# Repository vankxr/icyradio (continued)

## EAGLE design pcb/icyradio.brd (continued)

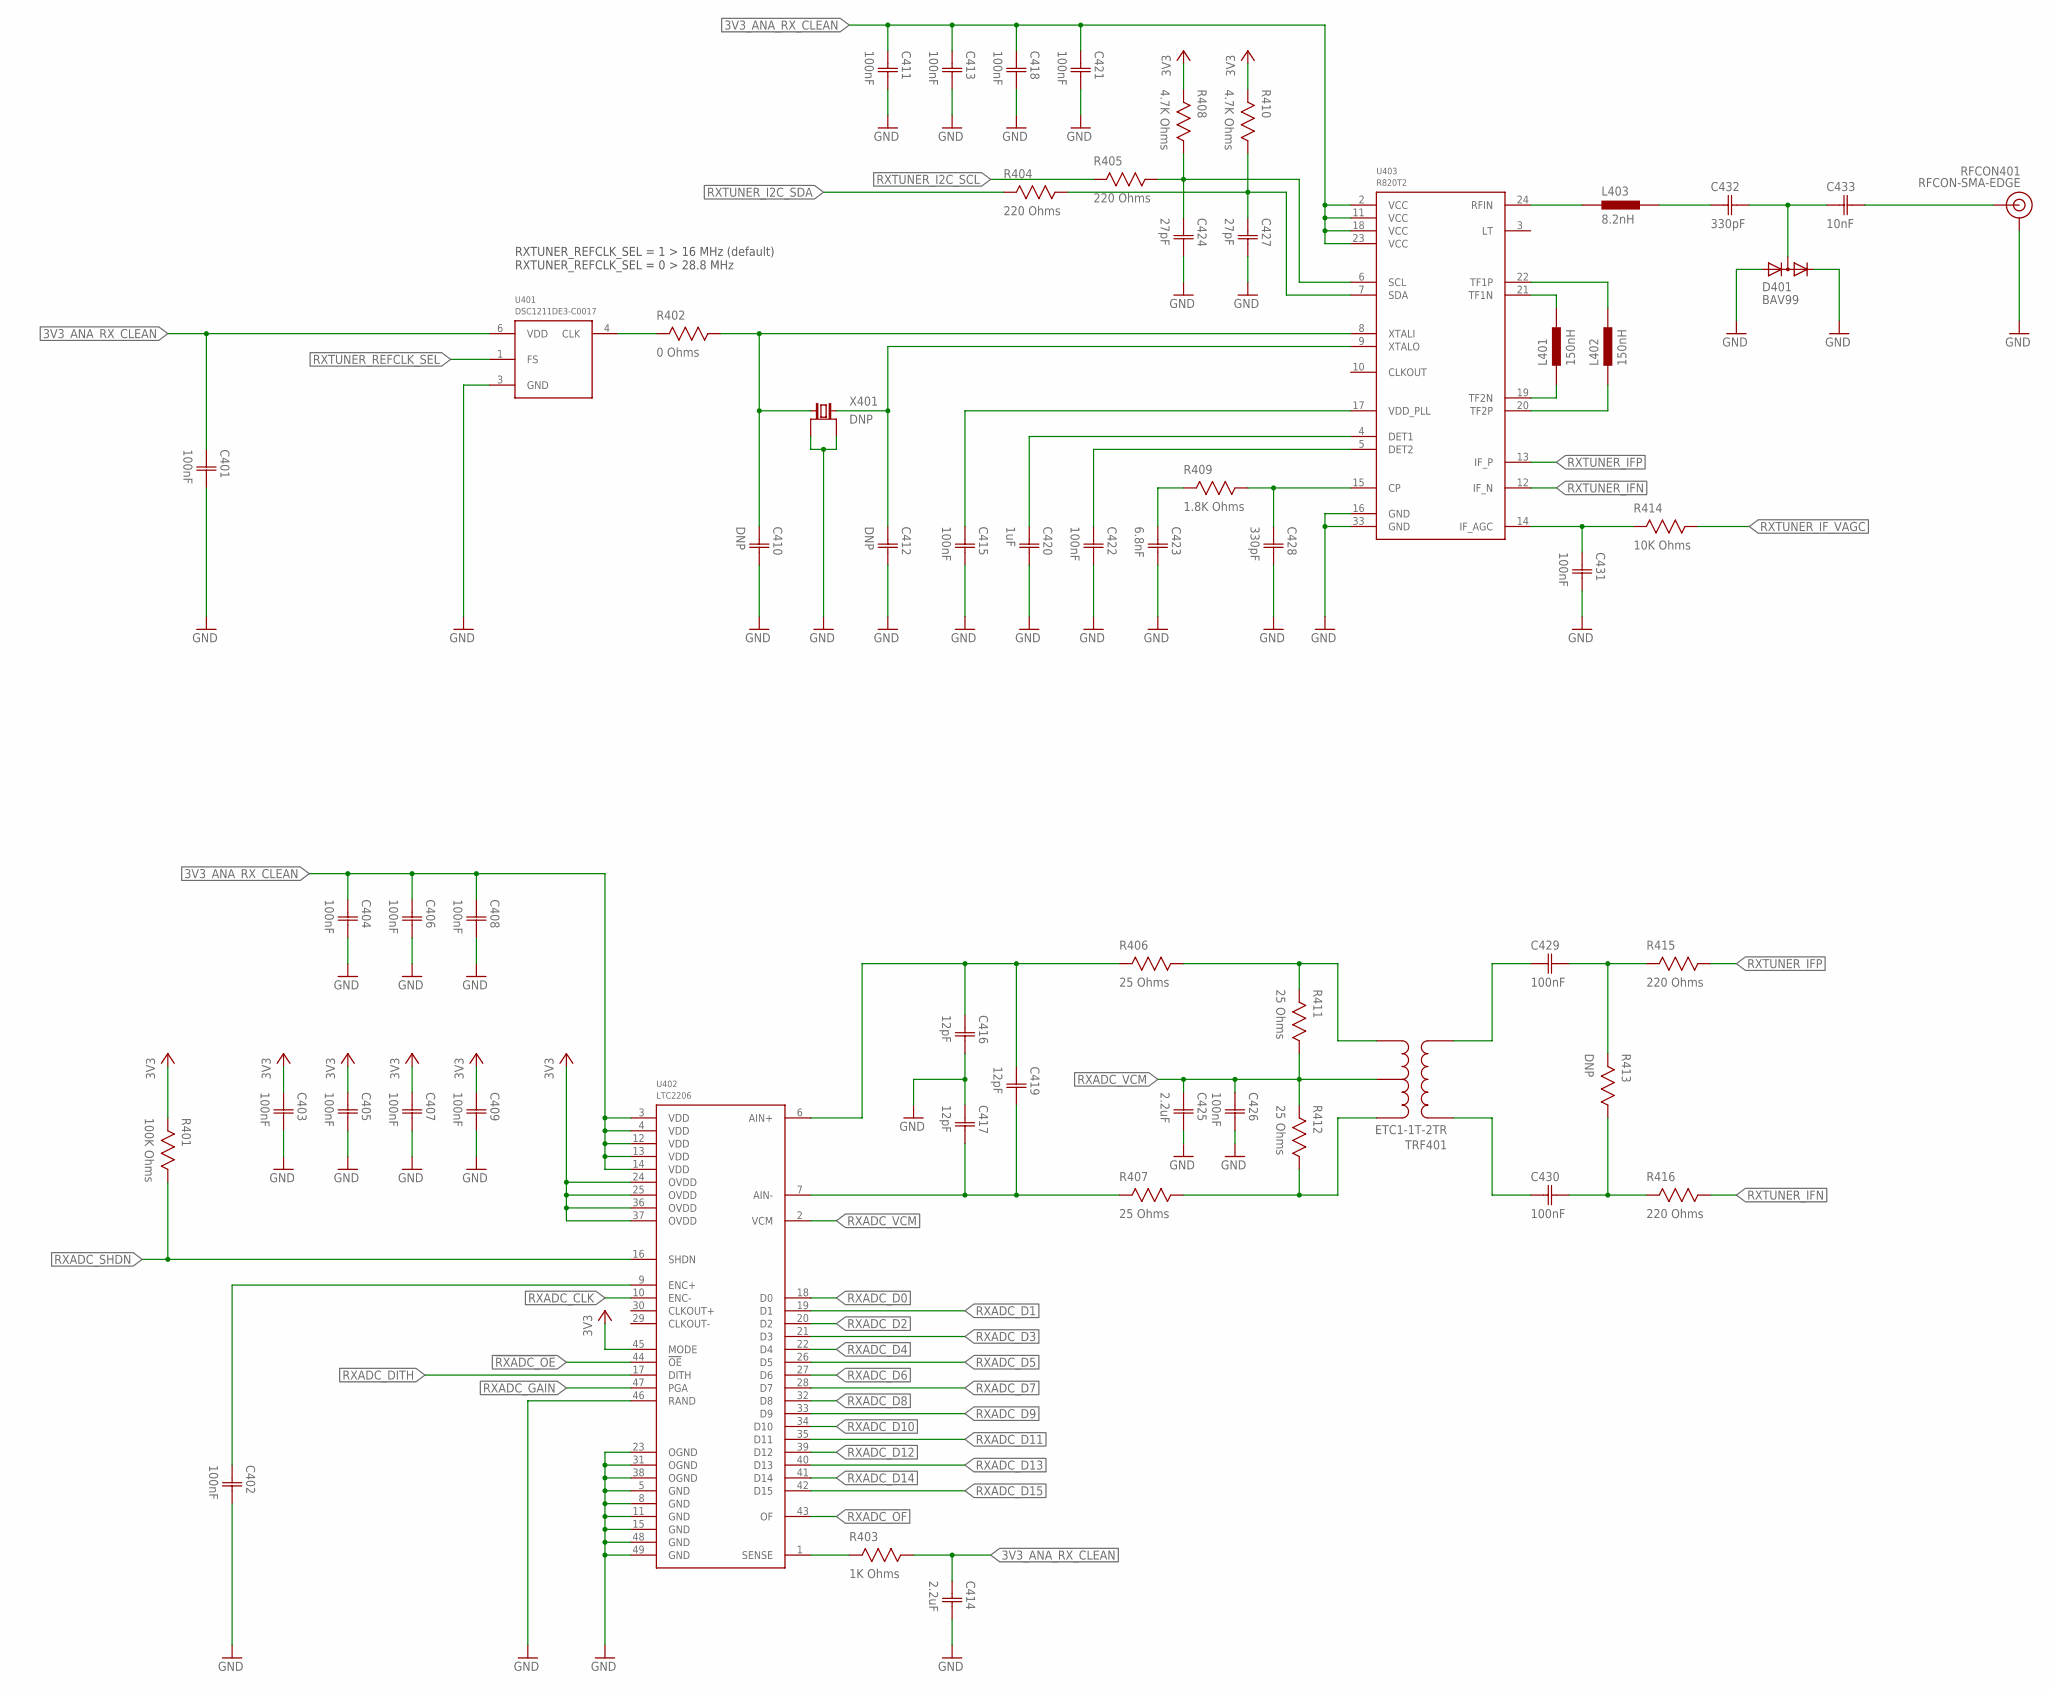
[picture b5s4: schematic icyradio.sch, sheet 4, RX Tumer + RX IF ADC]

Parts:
C401, C402, C403, C404, C405, C406, C407, C408, C409, C411, C413, C415, C418, C421, C422, C426, C429, C430, C431: 100nF; CAP0603
C410, C412: DNP; CAP0603
C414, C425: 2.2uF; CAP0603
C416, C417, C419: 12pF; CAP0603
C420: 1uF; CAP0603
C423: 6.8nF; CAP0603
C424, C427: 27pF; CAP0603
C428, C432: 330pF; CAP0603
C433: 10nF; CAP0603
D401: BAV99; SOT23
L401, L402: 150nH; IND0603
L403: 8.2nH; IND0603
R401: 100K Ohms; RES0603
R402: 0 Ohms; RES0603
R403: 1K Ohms; RES0603
R404, R405, R415, R416: 220 Ohms; RES0603
R406, R407, R411, R412: 25 Ohms; RES0603
R408, R410: 4.7K Ohms; RES0603
R409: 1.8K Ohms; RES0603
R413: DNP; RES0603
R414: 10K Ohms; RES0603
RFCON401: RFCON-SMA-EDGE; SMA-EDGE
TRF401: ETC1-1T-2TR; TRF-SM-22
U401: DSC1211DE3-C0017; VDFN6
U402: LTC2206; QFN48
U403: R820T2; QFN24
X401: DNP; 4-SMD-3225

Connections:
3V3: C403.1 (C1), C405.1 (C1), C407.1 (C1), C409.1 (C1), R401.2, R408.2, R410.2, U402.24 (OVDD), U402.25 (OVDD), U402.36 (OVDD), U402.37 (OVDD), U402.45 (MODE); also elsewhere on the board
3V3_ANA_RX_CLEAN: C401.1 (C1), C404.1 (C1), C406.1 (C1), C408.1 (C1), C411.1 (C1), C413.1 (C1), C414.1 (C1), C418.1 (C1), C421.1 (C1), R403.1, U401.6 (VDD), U402.3 (VDD), U402.4 (VDD), U402.12 (VDD), U402.13 (VDD), U402.14 (VDD), U403.2 (VCC), U403.11 (VCC), U403.18 (VCC), U403.23 (VCC); also elsewhere on the board
!RXADC_OE: U402.44 (!OE); also elsewhere on the board
GND: C401.2 (C2), C402.2 (C2), C403.2 (C2), C404.2 (C2), C405.2 (C2), C406.2 (C2), C407.2 (C2), C408.2 (C2), C409.2 (C2), C410.2 (C2), C411.2 (C2), C412.2 (C2), C413.2 (C2), C414.2 (C2), C415.2 (C2), C416.2 (C2), C417.1 (C1), C418.2 (C2), C420.2 (C2), C421.2 (C2), C422.2 (C2), C423.2 (C2), C424.2 (C2), C425.2 (C2), C426.2 (C2), C427.2 (C2), C428.2 (C2), C431.2 (C2), D401.1 (A), D401.2 (C), RFCON401.GND@0 (GND), RFCON401.GND@1 (GND), RFCON401.GND@2 (GND), RFCON401.GND@3 (GND), U401.3 (GND), U402.5 (GND), U402.8 (GND), U402.11 (GND), U402.15 (GND), U402.23 (OGND), U402.31 (OGND), U402.38 (OGND), U402.46 (RAND), U402.48 (GND), U402.49 (GND), U403.16 (GND), U403.33 (GND), X401.1 (GND), X401.3 (GND); also elsewhere on the board
unnamed: R407.1, R412.1, TRF401.3 (SEC1)
unnamed: C430.1 (C1), TRF401.4 (PRI1)
unnamed: R406.1, R411.2, TRF401.1 (SEC2)
unnamed: C429.1 (C1), TRF401.5 (PRI2)
unnamed: C430.2 (C2), R413.1, R416.2
unnamed: C429.2 (C2), R413.2, R415.2
unnamed: C433.2 (C2), RFCON401.SIG (SIGNAL)
unnamed: C432.2 (C2), C433.1 (C1), D401.3 (MID)
unnamed: C432.1 (C1), L403.2
unnamed: L403.1, U403.24 (RFIN)
unnamed: C424.1 (C1), R405.1, R408.1, U403.6 (SCL)
unnamed: C427.1 (C1), R404.1, R410.1, U403.7 (SDA)
unnamed: C423.1 (C1), R409.2
unnamed: R402.2, U401.4 (CLK)
unnamed: C431.1 (C1), R414.2, U403.14 (IF_AGC)
RXADC_AIN+: C416.1 (C1), C419.1 (C1), R406.2, U402.6 (AIN+)
RXADC_AIN-: C417.2 (C2), C419.2 (C2), R407.2, U402.7 (AIN-)
RXADC_CLK: U402.10 (ENC-); also elsewhere on the board
RXADC_D0: U402.18 (D0); also elsewhere on the board
RXADC_D1: U402.19 (D1); also elsewhere on the board
RXADC_D2: U402.20 (D2); also elsewhere on the board
RXADC_D3: U402.21 (D3); also elsewhere on the board
RXADC_D4: U402.22 (D4); also elsewhere on the board
RXADC_D5: U402.26 (D5); also elsewhere on the board
RXADC_D6: U402.27 (D6); also elsewhere on the board
RXADC_D7: U402.28 (D7); also elsewhere on the board
RXADC_D8: U402.32 (D8); also elsewhere on the board
RXADC_D9: U402.33 (D9); also elsewhere on the board
RXADC_D10: U402.34 (D10); also elsewhere on the board
RXADC_D11: U402.35 (D11); also elsewhere on the board
RXADC_D12: U402.39 (D12); also elsewhere on the board
RXADC_D13: U402.40 (D13); also elsewhere on the board
RXADC_D14: U402.41 (D14); also elsewhere on the board
RXADC_D15: U402.42 (D15); also elsewhere on the board
RXADC_DITH: U402.17 (DITH); also elsewhere on the board
RXADC_ENC+: C402.1 (C1), U402.9 (ENC+)
RXADC_GAIN: U402.47 (PGA); also elsewhere on the board
RXADC_OF: U402.43 (OF); also elsewhere on the board
RXADC_SENSE: R403.2, U402.1 (SENSE)
RXADC_SHDN: R401.1, U402.16 (SHDN); also elsewhere on the board
RXADC_VCM: C425.1 (C1), C426.1 (C1), R411.1, R412.2, TRF401.2 (CT), U402.2 (VCM)
RXTUNER_DET1: C420.1 (C1), U403.4 (DET1)
RXTUNER_DET2: C422.1 (C1), U403.5 (DET2)
RXTUNER_I2C_SCL: R405.2; also elsewhere on the board
RXTUNER_I2C_SDA: R404.2; also elsewhere on the board
RXTUNER_IFN: R416.1, U403.12 (IF_N)
RXTUNER_IFP: R415.1, U403.13 (IF_P)
RXTUNER_IF_VAGC: R414.1; also elsewhere on the board
RXTUNER_PLL_CP: C428.1 (C1), R409.1, U403.15 (CP)
RXTUNER_REFCLK_SEL: U401.1 (FS); also elsewhere on the board
RXTUNER_TF1N: L401.2, U403.21 (TF1N)
RXTUNER_TF1P: L402.2, U403.22 (TF1P)
RXTUNER_TF2N: L401.1, U403.19 (TF2N)
RXTUNER_TF2P: L402.1, U403.20 (TF2P)
RXTUNER_VDD_PLL: C415.1 (C1), U403.17 (VDD_PLL)
RXTUNER_XTALI: C410.1 (C1), R402.1, U403.8 (XTALI), X401.2 (1)
RXTUNER_XTALO: C412.1 (C1), U403.9 (XTALO), X401.4 (2)

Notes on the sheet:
RXTUNER_REFCLK_SEL = 1 > 16 MHz (default) RXTUNER_REFCLK_SEL = 0 > 28.8 MHz

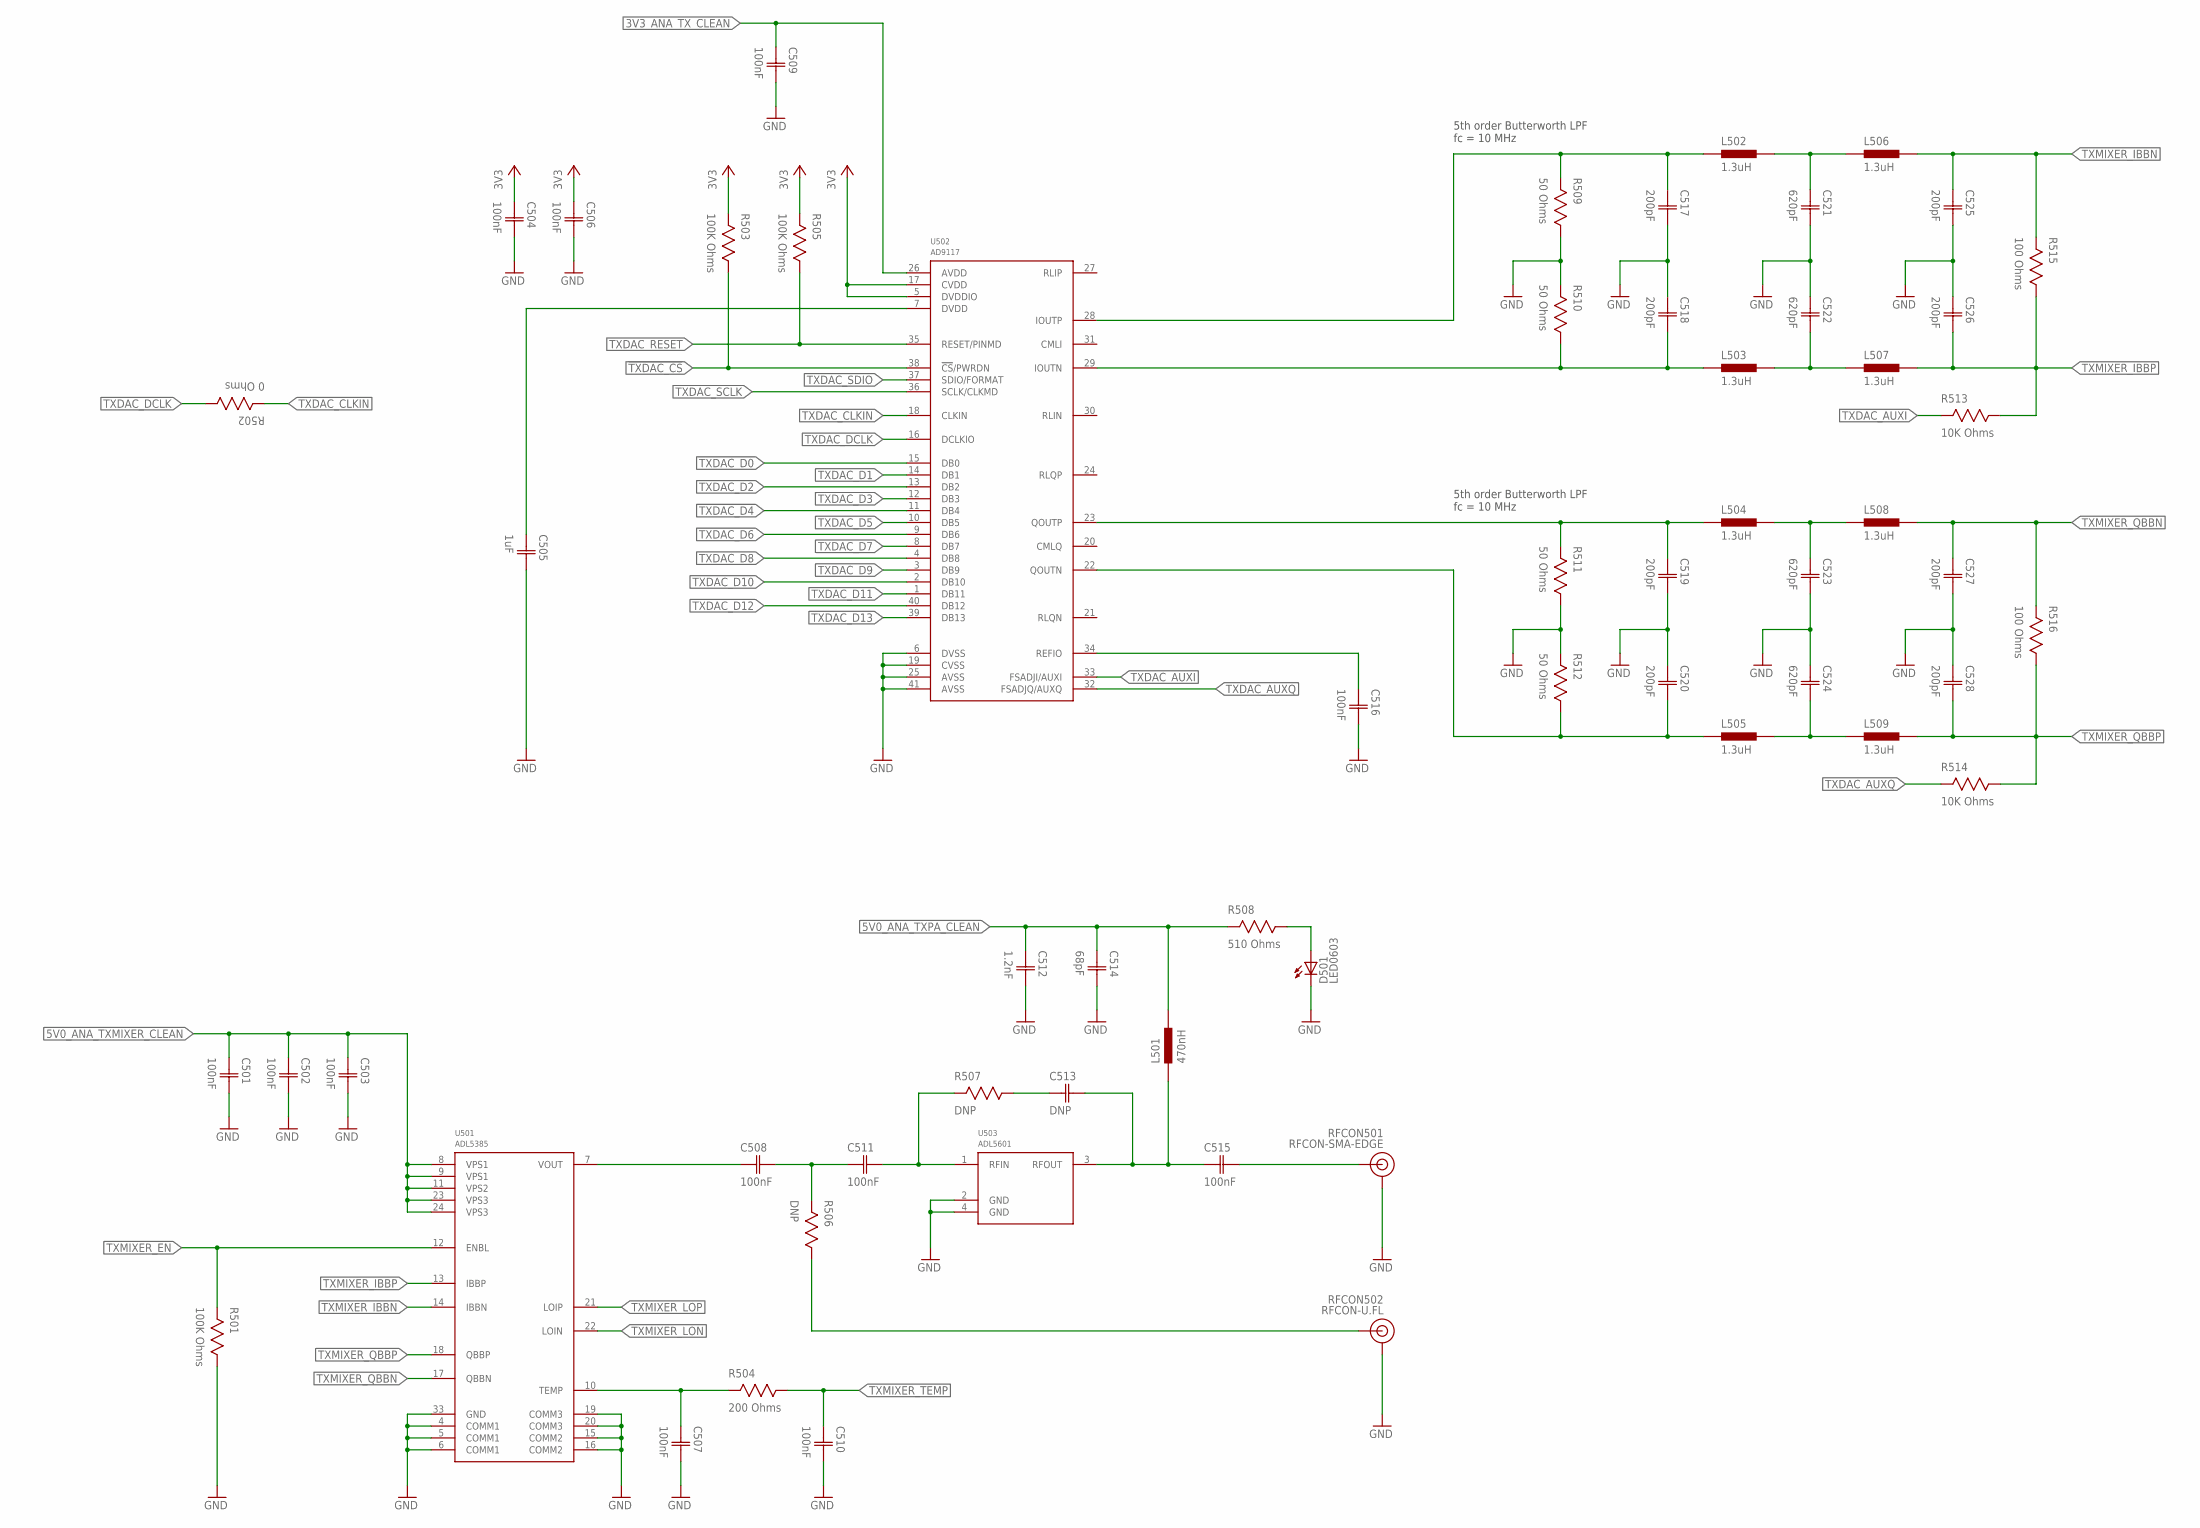
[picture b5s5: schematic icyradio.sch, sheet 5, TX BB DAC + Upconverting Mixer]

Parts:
C501, C502, C503, C504, C506, C507, C508, C509, C510, C511, C515, C516: 100nF; CAP0603
C505: 1uF; CAP0603
C512: 1.2nF; CAP0603
C513: DNP; CAP0603
C514: 68pF; CAP0603
C517, C518, C519, C520, C525, C526, C527, C528: 200pF; CAP0603
C521, C522, C523, C524: 620pF; CAP0603
D501: LED0603; 0603
L501: 470nH; IND0603
L502, L503, L504, L505, L506, L507, L508, L509: 1.3uH; IND0603
R501, R503, R505: 100K Ohms; RES0603
R502: 0 Ohms; RES0603
R504: 200 Ohms; RES0603
R506, R507: DNP; RES0603
R508: 510 Ohms; RES0603
R509, R510, R511, R512: 50 Ohms; RES0603
R513, R514: 10K Ohms; RES0603
R515, R516: 100 Ohms; RES0603
RFCON501: RFCON-SMA-EDGE; SMA-EDGE
RFCON502: RFCON-U.FL; U.FL
U501: ADL5385; QFN24
U502: AD9117; QFN40
U503: ADL5601; SOT89

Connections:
3V3: C504.1 (C1), C506.1 (C1), R503.2, R505.2, U502.5 (DVDDIO), U502.17 (CVDD); also elsewhere on the board
3V3_ANA_TX_CLEAN: C509.1 (C1), U502.26 (AVDD); also elsewhere on the board
5V0_ANA_TXMIXER_CLEAN: C501.1 (C1), C502.1 (C1), C503.1 (C1), U501.8 (VPS1), U501.9 (VPS1), U501.11 (VPS2), U501.23 (VPS3), U501.24 (VPS3); also elsewhere on the board
5V0_ANA_TXPA_CLEAN: C512.1 (C1), C514.1 (C1), L501.2, R508.2; also elsewhere on the board
!TXDAC_CS: R503.1, U502.38 (!CS!/PWRDN); also elsewhere on the board
GND: C501.2 (C2), C502.2 (C2), C503.2 (C2), C504.2 (C2), C505.2 (C2), C506.2 (C2), C507.2 (C2), C509.2 (C2), C510.2 (C2), C512.2 (C2), C514.2 (C2), C516.2 (C2), C517.2 (C2), C518.1 (C1), C519.2 (C2), C520.1 (C1), C521.2 (C2), C522.1 (C1), C523.2 (C2), C524.1 (C1), C525.2 (C2), C526.1 (C1), C527.2 (C2), C528.1 (C1), D501.1 (C), R501.1, R509.1, R510.2, R511.1, R512.2, RFCON501.GND@0 (GND), RFCON501.GND@1 (GND), RFCON501.GND@2 (GND), RFCON501.GND@3 (GND), RFCON502.P$1 (GND), RFCON502.P$2 (GND), U501.4 (COMM1), U501.5 (COMM1), U501.6 (COMM1), U501.15 (COMM2), U501.16 (COMM2), U501.19 (COMM3), U501.20 (COMM3), U501.33 (GND), U502.6 (DVSS), U502.19 (CVSS), U502.20 (CMLQ), U502.25 (AVSS), U502.31 (CMLI), U502.41 (AVSS), U503.2 (GND), U503.4 (GND); also elsewhere on the board
unnamed: C508.2 (C2), C511.1 (C1), R506.2
unnamed: C507.1 (C1), R504.2, U501.10 (TEMP)
unnamed: C515.2 (C2), RFCON501.SIG (SIGNAL)
unnamed: C508.1 (C1), U501.7 (VOUT)
unnamed: C518.2 (C2), L503.1, R510.1, U502.29 (IOUTN)
unnamed: C517.1 (C1), L502.1, R509.2, U502.28 (IOUTP)
unnamed: C522.2 (C2), L503.2, L507.1
unnamed: C521.1 (C1), L502.2, L506.1
unnamed: C505.1 (C1), U502.7 (DVDD)
unnamed: C520.2 (C2), L505.1, R512.1, U502.22 (QOUTN)
unnamed: C519.1 (C1), L504.1, R511.2, U502.23 (QOUTP)
unnamed: C524.2 (C2), L505.2, L509.1
unnamed: C523.1 (C1), L504.2, L508.1
unnamed: C513.1 (C1), R507.1
unnamed: C516.1 (C1), U502.34 (REFIO)
unnamed: D501.2 (A), R508.1
TXDAC_AUXI: R513.2, U502.33 (FSADJI/AUXI)
TXDAC_AUXQ: R514.2, U502.32 (FSADJQ/AUXQ)
TXDAC_CLKIN: R502.2, U502.18 (CLKIN); also elsewhere on the board
TXDAC_D0: U502.15 (DB0); also elsewhere on the board
TXDAC_D1: U502.14 (DB1); also elsewhere on the board
TXDAC_D2: U502.13 (DB2); also elsewhere on the board
TXDAC_D3: U502.12 (DB3); also elsewhere on the board
TXDAC_D4: U502.11 (DB4); also elsewhere on the board
TXDAC_D5: U502.10 (DB5); also elsewhere on the board
TXDAC_D6: U502.9 (DB6); also elsewhere on the board
TXDAC_D7: U502.8 (DB7); also elsewhere on the board
TXDAC_D8: U502.4 (DB8); also elsewhere on the board
TXDAC_D9: U502.3 (DB9); also elsewhere on the board
TXDAC_D10: U502.2 (DB10); also elsewhere on the board
TXDAC_D11: U502.1 (DB11); also elsewhere on the board
TXDAC_D12: U502.40 (DB12); also elsewhere on the board
TXDAC_D13: U502.39 (DB13); also elsewhere on the board
TXDAC_DCLK: R502.1, U502.16 (DCLKIO); also elsewhere on the board
TXDAC_RESET: R505.1, U502.35 (RESET/PINMD); also elsewhere on the board
TXDAC_SCLK: U502.36 (SCLK/CLKMD); also elsewhere on the board
TXDAC_SDIO: U502.37 (SDIO/FORMAT); also elsewhere on the board
TXMIXER_EN: R501.2, U501.12 (ENBL); also elsewhere on the board
TXMIXER_IBBN: C525.1 (C1), L506.2, R515.2, U501.14 (IBBN)
TXMIXER_IBBP: C526.2 (C2), L507.2, R513.1, R515.1, U501.13 (IBBP)
TXMIXER_LON: U501.22 (LOIN); also elsewhere on the board
TXMIXER_LOP: U501.21 (LOIP); also elsewhere on the board
TXMIXER_OUT: R506.1, RFCON502.P$3 (SIGNAL)
TXMIXER_QBBN: C527.1 (C1), L508.2, R516.2, U501.17 (QBBN)
TXMIXER_QBBP: C528.2 (C2), L509.2, R514.1, R516.1, U501.18 (QBBP)
TXMIXER_TEMP: C510.1 (C1), R504.1; also elsewhere on the board
TXPA_IN: C511.2 (C2), R507.2, U503.1 (RFIN)
TXPA_OUT: C513.2 (C2), C515.1 (C1), L501.1, U503.3 (RFOUT)

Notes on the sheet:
5th order Butterworth LPF fc = 10 MHz

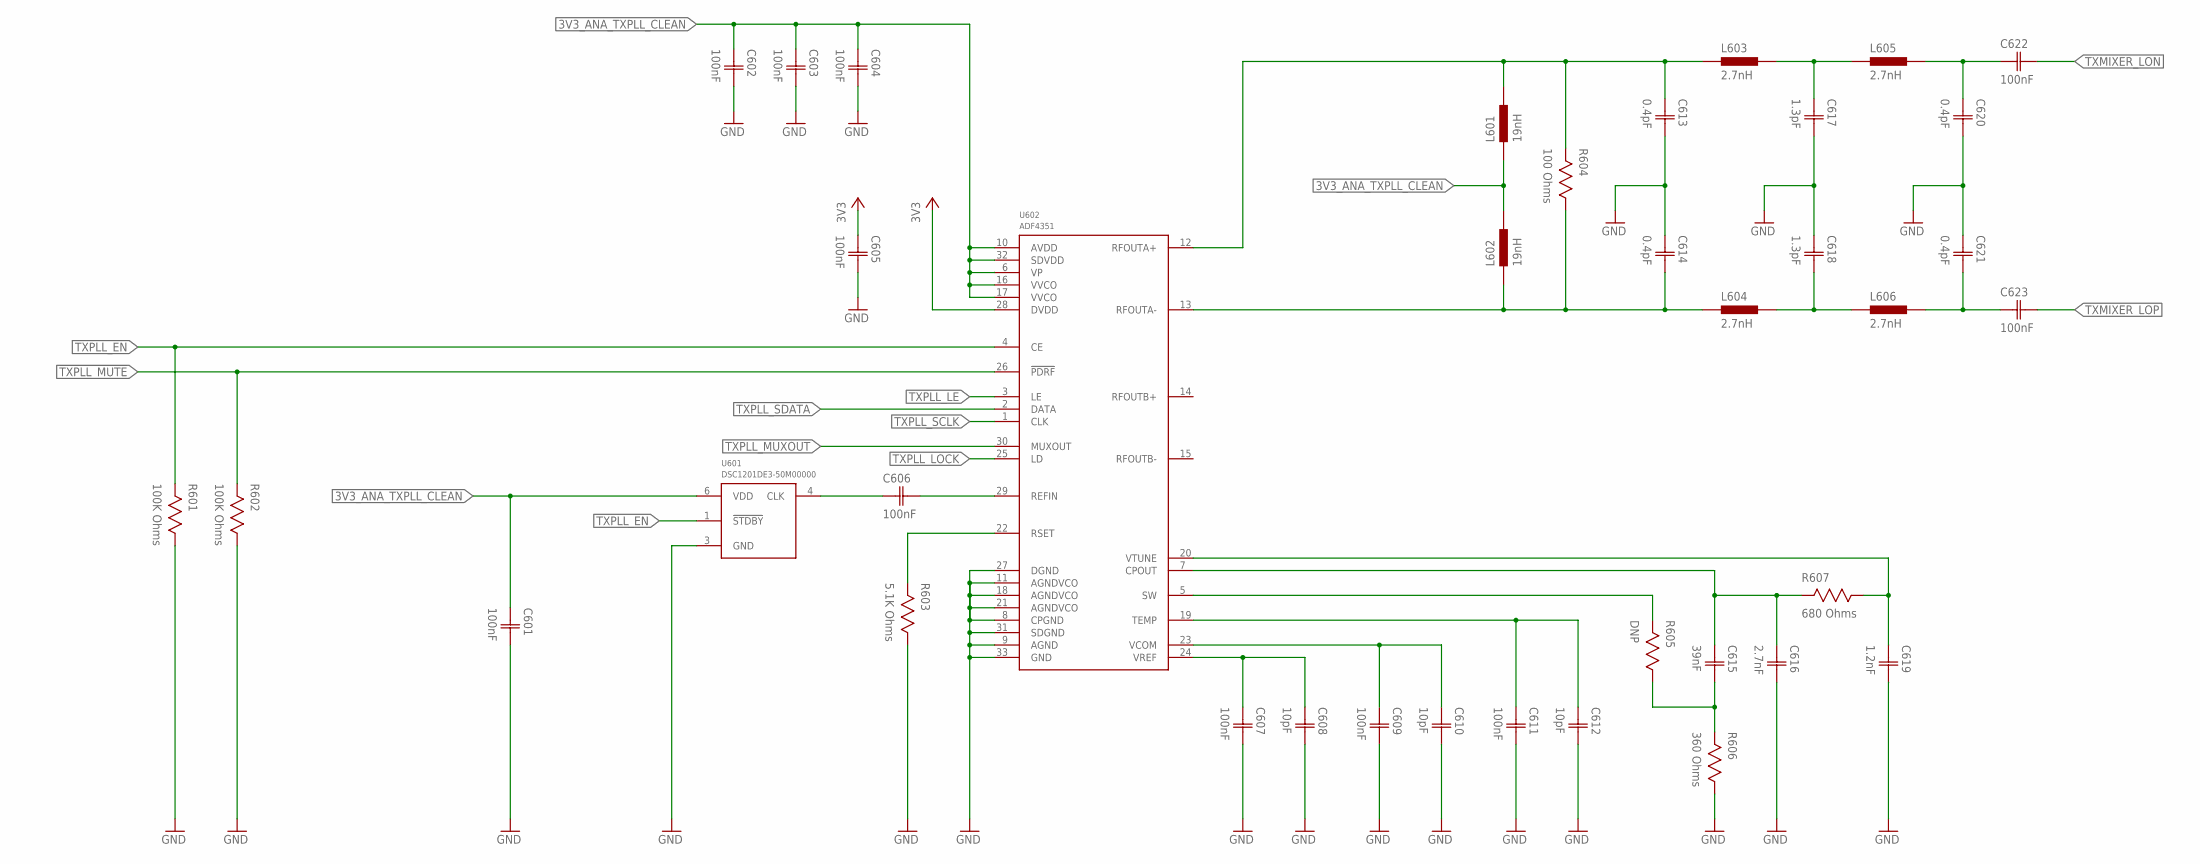
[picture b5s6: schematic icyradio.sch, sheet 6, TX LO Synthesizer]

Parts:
C601, C602, C603, C604, C605, C606, C607, C609, C611, C622, C623: 100nF; CAP0603
C608, C610, C612: 10pF; CAP0603
C613, C614, C620, C621: 0.4pF; CAP0603
C615: 39nF; CAP0603
C616: 2.7nF; CAP0603
C617, C618: 1.3pF; CAP0603
C619: 1.2nF; CAP0603
L601, L602: 19nH; IND0603
L603, L604, L605, L606: 2.7nH; IND0603
R601, R602: 100K Ohms; RES0603
R603: 5.1K Ohms; RES0603
R604: 100 Ohms; RES0603
R605: DNP; RES0603
R606: 360 Ohms; RES0603
R607: 680 Ohms; RES0603
U601: DSC1201DE3-50M00000; VDFN6
U602: ADF4351; QFN32

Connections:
3V3: C605.1 (C1), U602.28 (DVDD); also elsewhere on the board
3V3_ANA_TXPLL_CLEAN: C601.1 (C1), C602.1 (C1), C603.1 (C1), C604.1 (C1), L601.1, L602.2, U601.6 (VDD), U602.6 (VP), U602.10 (AVDD), U602.16 (VVCO), U602.17 (VVCO), U602.32 (SDVDD); also elsewhere on the board
!TXPLL_MUTE: R602.2, U602.26 (!PDRF); also elsewhere on the board
GND: C601.2 (C2), C602.2 (C2), C603.2 (C2), C604.2 (C2), C605.2 (C2), C607.2 (C2), C608.2 (C2), C609.2 (C2), C610.2 (C2), C611.2 (C2), C612.2 (C2), C613.2 (C2), C614.1 (C1), C616.2 (C2), C617.2 (C2), C618.1 (C1), C619.2 (C2), C620.2 (C2), C621.1 (C1), R601.1, R602.1, R603.1, R606.1, U601.3 (GND), U602.8 (CPGND), U602.9 (AGND), U602.11 (AGNDVCO), U602.18 (AGNDVCO), U602.21 (AGNDVCO), U602.27 (DGND), U602.31 (SDGND), U602.33 (GND); also elsewhere on the board
unnamed: C614.2 (C2), L602.1, L604.1, R604.1, U602.13 (RFOUTA-)
unnamed: C618.2 (C2), L604.2, L606.1
unnamed: C613.1 (C1), L601.2, L603.1, R604.2, U602.12 (RFOUTA+)
unnamed: C617.1 (C1), L603.2, L605.1
unnamed: C620.1 (C1), C622.1 (C1), L605.2
unnamed: C621.2 (C2), C623.1 (C1), L606.2
unnamed: C615.2 (C2), R605.1, R606.2
unnamed: R603.2, U602.22 (RSET)
TXMIXER_LON: C622.2 (C2); also elsewhere on the board
TXMIXER_LOP: C623.2 (C2); also elsewhere on the board
TXPLL_CP_VOUT: C615.1 (C1), C616.1 (C1), R607.2, U602.7 (CPOUT)
TXPLL_EN: R601.2, U601.1 (!STDBY), U602.4 (CE); also elsewhere on the board
TXPLL_FASTLOCK_SW: R605.2, U602.5 (SW)
TXPLL_LE: U602.3 (LE); also elsewhere on the board
TXPLL_LOCK: U602.25 (LD); also elsewhere on the board
TXPLL_MUXOUT: U602.30 (MUXOUT); also elsewhere on the board
TXPLL_REF_ACC: C606.2 (C2), U602.29 (REFIN)
TXPLL_REF_DCC: C606.1 (C1), U601.4 (CLK)
TXPLL_SCLK: U602.1 (CLK); also elsewhere on the board
TXPLL_SDATA: U602.2 (DATA); also elsewhere on the board
TXPLL_TEMP: C611.1 (C1), C612.1 (C1), U602.19 (TEMP)
TXPLL_VCOM: C609.1 (C1), C610.1 (C1), U602.23 (VCOM)
TXPLL_VREF: C607.1 (C1), C608.1 (C1), U602.24 (VREF)
TXPLL_VTUNE: C619.1 (C1), R607.1, U602.20 (VTUNE)

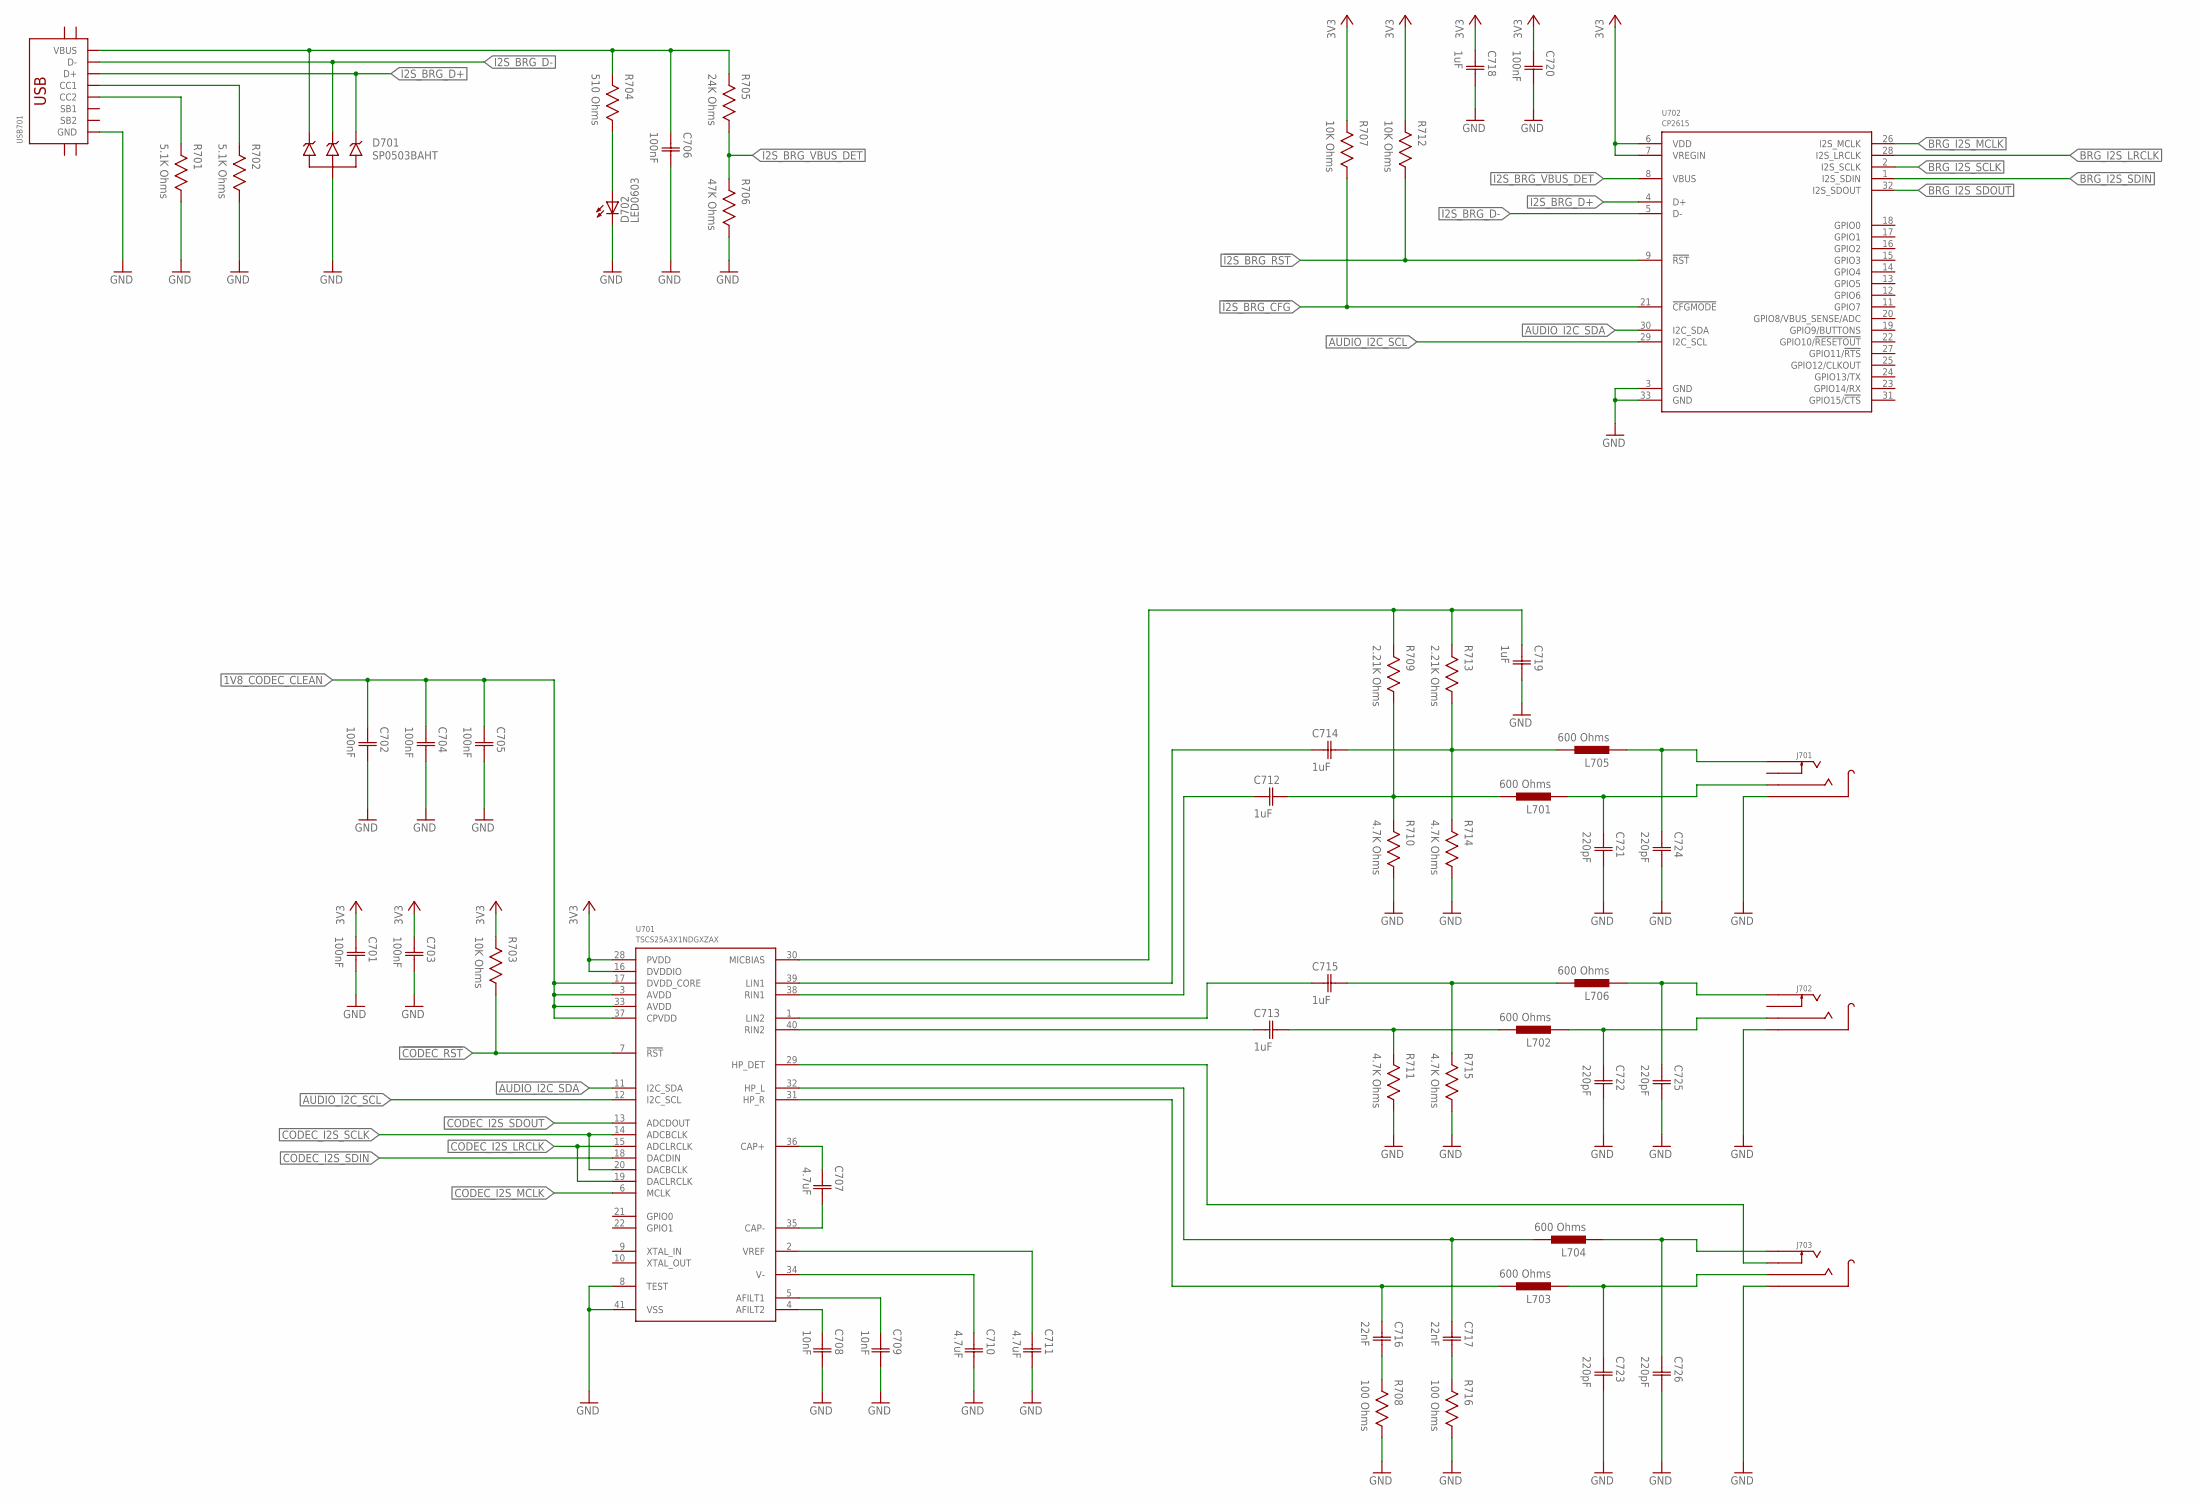
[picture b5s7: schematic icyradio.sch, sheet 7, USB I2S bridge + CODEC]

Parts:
C701, C702, C703, C704, C705, C706, C720: 100nF; CAP0603
C707, C710, C711: 4.7uF; CAP0603
C708, C709: 10nF; CAP0603
C712, C713, C714, C715, C718, C719: 1uF; CAP0603
C716, C717: 22nF; CAP0603
C721, C722, C723, C724, C725, C726: 220pF; CAP0603
D701: SP0503BAHT; SOT143
D702: LED0603; 0603
J701, J702, J703: TRSJACK; 3.5TRSJACK
L701, L702, L703, L704, L705, L706: 600 Ohms; IND0603
R701, R702: 5.1K Ohms; RES0603
R703, R707, R712: 10K Ohms; RES0603
R704: 510 Ohms; RES0603
R705: 24K Ohms; RES0603
R706: 47K Ohms; RES0603
R708, R716: 100 Ohms; RES0603
R709, R713: 2.21K Ohms; RES0603
R710, R711, R714, R715: 4.7K Ohms; RES0603
U701: TSCS25A3X1NDGXZAX; QFN40
U702: CP2615; QFN32
USB701: USB-C-16P-SMD-FLAT-SIDE-TYPE-2

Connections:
1V8_CODEC_CLEAN: C702.1 (C1), C704.1 (C1), C705.1 (C1), U701.3 (AVDD), U701.17 (DVDD_CORE), U701.33 (AVDD), U701.37 (CPVDD); also elsewhere on the board
3V3: C701.1 (C1), C703.1 (C1), C718.1 (C1), C720.1 (C1), R703.2, R707.2, R712.2, U701.16 (DVDDIO), U701.28 (PVDD), U702.6 (VDD), U702.7 (VREGIN); also elsewhere on the board
!CODEC_RST: R703.1, U701.7 (!RST); also elsewhere on the board
!I2S_BRG_CFG: R707.1, U702.21 (!CFGMODE); also elsewhere on the board
!I2S_BRG_RST: R712.1, U702.9 (!RST); also elsewhere on the board
AUDIO_I2C_SCL: U701.12 (I2C_SCL), U702.29 (I2C_SCL); also elsewhere on the board
AUDIO_I2C_SDA: U701.11 (I2C_SDA), U702.30 (I2C_SDA); also elsewhere on the board
BRG_I2S_LRCLK: U702.28 (I2S_LRCLK); also elsewhere on the board
BRG_I2S_MCLK: U702.26 (I2S_MCLK); also elsewhere on the board
BRG_I2S_SCLK: U702.2 (I2S_SCLK); also elsewhere on the board
BRG_I2S_SDIN: U702.1 (I2S_SDIN); also elsewhere on the board
BRG_I2S_SDOUT: U702.32 (I2S_SDOUT); also elsewhere on the board
CODEC_AFILT1: C709.1 (C1), U701.5 (AFILT1)
CODEC_AFILT2: C708.1 (C1), U701.4 (AFILT2)
CODEC_CAP-: C707.2 (C2), U701.35 (CAP-)
CODEC_HP_L: C726.1 (C1), J703.2 (T), L704.1
CODEC_HP_R: C723.1 (C1), J703.3 (R), L703.1
CODEC_I2S_LRCLK: U701.15 (ADCLRCLK), U701.19 (DACLRCLK); also elsewhere on the board
CODEC_I2S_MCLK: U701.6 (MCLK); also elsewhere on the board
CODEC_I2S_SCLK: U701.14 (ADCBCLK), U701.20 (DACBCLK); also elsewhere on the board
CODEC_I2S_SDIN: U701.18 (DACDIN); also elsewhere on the board
CODEC_I2S_SDOUT: U701.13 (ADCDOUT); also elsewhere on the board
CODEC_LINE_L: C725.1 (C1), J702.2 (T), L706.1
CODEC_LINE_R: C722.1 (C1), J702.3 (R), L702.1
CODEC_MIC_L: C724.1 (C1), J701.2 (T), L705.1
CODEC_MIC_R: C721.1 (C1), J701.3 (R), L701.1
CODEC_V-: C710.1 (C1), U701.34 (V-)
CODEC_VREF: C711.1 (C1), U701.2 (VREF)
CPDEC_CAP+: C707.1 (C1), U701.36 (CAP+)
GND: C701.2 (C2), C702.2 (C2), C703.2 (C2), C704.2 (C2), C705.2 (C2), C706.2 (C2), C708.2 (C2), C709.2 (C2), C710.2 (C2), C711.2 (C2), C718.2 (C2), C719.2 (C2), C720.2 (C2), C721.2 (C2), C722.2 (C2), C723.2 (C2), C724.2 (C2), C725.2 (C2), C726.2 (C2), D701.1, D702.1 (C), J701.1 (S), J702.1 (S), J703.1 (S), R701.1, R702.1, R706.1, R708.1, R710.1, R711.1, R714.1, R715.1, R716.1, U701.8 (TEST), U701.41 (VSS), U702.3 (GND), U702.33 (GND), USB701.A1/B12 (GND), USB701.B1/A12 (GND); also elsewhere on the board
I2S_BRG_D+: D701.4, U702.4 (D+), USB701.A6 (D+), USB701.B6 (D+)
I2S_BRG_D-: D701.3, U702.5 (D-), USB701.A7 (D-), USB701.B7 (D-)
I2S_BRG_VBUS: C706.1 (C1), D701.2, R704.2, R705.2, USB701.A4/B9 (VBUS), USB701.B4/A9 (VBUS)
I2S_BRG_VBUS_DET: R705.1, R706.2, U702.8 (VBUS)
unnamed: R701.2, USB701.B5 (CC2)
unnamed: R702.2, USB701.A5 (CC1)
unnamed: C712.2 (C2), L701.2, R709.1, R710.2
unnamed: C714.2 (C2), L705.2, R713.1, R714.2
unnamed: C713.2 (C2), L702.2, R711.2
unnamed: C715.2 (C2), L706.2, R715.2
unnamed: C712.1 (C1), U701.38 (RIN1)
unnamed: C713.1 (C1), U701.40 (RIN2)
unnamed: C714.1 (C1), U701.39 (LIN1)
unnamed: C717.1 (C1), L704.2, U701.32 (HP_L)
unnamed: J703.4 (DT), U701.29 (HP_DET)
unnamed: C716.2 (C2), R708.2
unnamed: C717.2 (C2), R716.2
unnamed: C716.1 (C1), L703.2, U701.31 (HP_R)
unnamed: C719.1 (C1), R709.2, R713.2, U701.30 (MICBIAS)
unnamed: C715.1 (C1), U701.1 (LIN2)
unnamed: D702.2 (A), R704.1
